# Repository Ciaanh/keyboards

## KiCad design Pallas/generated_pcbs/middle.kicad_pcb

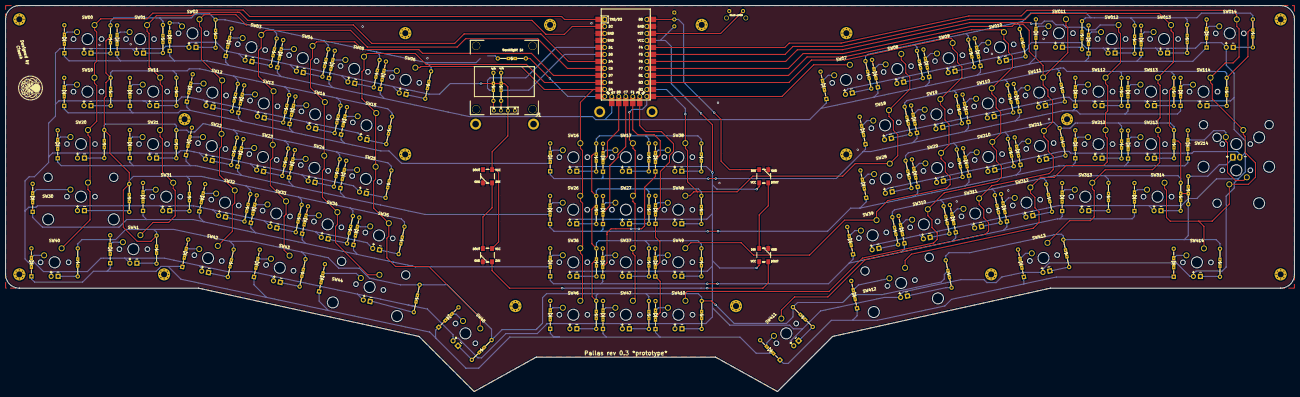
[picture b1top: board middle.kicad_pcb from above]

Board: 2 copper layers, 467.5 x 140.0 mm, 259 parts (1 on the bottom side), 182 nets.

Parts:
D00, D01, D02, D03, D04, D05, D06, D07, D08, D09, D010, D10, D11, D011, D12, D012, D13, D013, D14, D014, D15, D16, D17, D18, D19, D20, D21, D22, D23, D24, D25, D26, D27, D28, D29, D30, D31, D32, D33, D34, D35, D36, D37, D38, D39, D40, D41, D42, D43, D44, D45, D46, D47, D48, D49, D110, D111, D112, D113, D114, D210, D211, D212, D213, D214, D310, D311, D312, D313, D314, D410, D411, D412, D413, D414: Diode; Diode_SMD_THT
J1: OLED; OLED_128x64_I2C
J2: RGB_LED; conn_3pins
LogoBaseMiddleTop: LOGO; Ciaanh_signature
LogoMiddle2: LOGO; athena
MountBaseMiddleTop0, MountBaseMiddleTop2, MountBaseMiddleTop3, MountBaseMiddleTop4, MountBaseMiddleTop5, MountBaseMiddleTop6, MountBaseMiddleTop7, MountBaseMiddleTop8, MountBaseMiddleTop9, MountBaseMiddleTop10, MountBaseMiddleTop11, MountBaseMiddleTop12, MountBaseMiddleTop13, MountBaseMiddleTop14, MountBaseMiddleTop15, MountBaseMiddleTop15#2: MountingHole; MountingHole_2.2mm_M2_Pad_Via
MountForMiddle1: HOLE; MountingHole_2.4mm_M2_Pad
MountMiddle1, MountMiddle2, MountMiddle3: HOLE; MountingHole_2.4mm_M2_Pad
Q1: IRLML6344TRPbF; SOT23-3_HSOL_Back
R00, R01, R02, R03, R04, R05, R06, R07, R08, R09, R10, R010, R11, R011, R012, R12, R13, R013, R014, R14, R15, R16, R17, R18, R19, R20, R21, R22, R23, R24, R25, R26, R27, R28, R29, R30, R31, R32, R33, R34, R35, R36, R37, R38, R39, R40, R41, R42, R43, R44, R45, R46, R47, R48, R49, R110, R111, R112, R113, R114, R210, R211, R212, R213, R214, R310, R311, R312, R313, R314, R410, R411, R412, R413, R414: 470; Resistors_SMD_THT
R1, R2: 4.7k; Resistors_SMD_THT
R3: 1K; Resistors_SMD_THT
RGB1, RGB2, RGB3, RGB4: WS2812B; WS2812B_Front
RSW0: SW_RST
SW00, SW01, SW02, SW03, SW04, SW05, SW06, SW07, SW08, SW09, SW010, SW011, SW11, SW012, SW12, SW013, SW13, SW014, SW14, SW15, SW16, SW17, SW18, SW19, SW21, SW22, SW23, SW24, SW25, SW26, SW27, SW28, SW29, SW31, SW32, SW33, SW34, SW35, SW36, SW37, SW38, SW39, SW43, SW46, SW47, SW48, SW49, SW110, SW111, SW112, SW113, SW114, SW210, SW211, SW212, SW213, SW310, SW311, SW312, SW313, SW410: SW_PUSH; SW_Cherry_MX_1.00u_PCB
SW10: SW_PUSH; SW_Cherry_MX_1.50u_PCB
SW20, SW314: SW_PUSH; SW_Cherry_MX_1.75u_PCB
SW30: SW_PUSH; SW_Cherry_MX_2.25u_PCB
SW40, SW41, SW42, SW45, SW411, SW413, SW414: SW_PUSH; SW_Cherry_MX_1.25u_PCB
SW44: SW_PUSH; SW_Cherry_MX_2.00u_PCB
SW214: SW_PUSH; SW_Cherry_MX_2.25u_ISO_PCB
SW412: SW_PUSH; SW_Cherry_MX_2.75u_PCB
U1: Elite-C; Elite-C-castellated-29pin-holes

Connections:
Backlight: R3.2, U1.12
GND: J1.1, J2.1, Q1.2, RGB1.3, RGB2.3, RGB3.3, RGB4.3, RSW0.1, U1.3, U1.4, U1.23
LED: Q1.3, R00.1, R01.1, R02.1, R03.1, R04.1, R05.1, R06.1, R07.1, R08.1, R09.1, R10.1, R010.1, R11.1, R011.1, R012.1, R12.1, R13.1, R013.1, R014.1, R14.1, R15.1, R16.1, R17.1, R18.1, R19.1, R20.1, R21.1, R22.1, R23.1, R24.1, R25.1, R26.1, R27.1, R28.1, R29.1, R30.1, R31.1, R32.1, R33.1, R34.1, R35.1, R36.1, R37.1, R38.1, R39.1, R40.1, R41.1, R42.1, R43.1, R44.1, R45.1, R46.1, R47.1, R48.1, R49.1, R110.1, R111.1, R112.1, R113.1, R114.1, R210.1, R211.1, R212.1, R213.1, R214.1, R310.1, R311.1, R312.1, R313.1, R314.1, R410.1, R411.1, R412.1, R413.1, R414.1
unnamed: D00.2, SW00.2
unnamed: D01.2, SW01.2
unnamed: D02.2, SW02.2
unnamed: D03.2, SW03.2
unnamed: D04.2, SW04.2
unnamed: D05.2, SW05.2
unnamed: D06.2, SW06.2
unnamed: D07.2, SW07.2
unnamed: D08.2, SW08.2
unnamed: D09.2, SW09.2
unnamed: D010.2, SW010.2
unnamed: D10.2, SW10.2
unnamed: D011.2, SW011.2
unnamed: D11.2, SW11.2
unnamed: D012.2, SW012.2
unnamed: D12.2, SW12.2
unnamed: D013.2, SW013.2
unnamed: D13.2, SW13.2
unnamed: D014.2, SW014.2
unnamed: D14.2, SW14.2
unnamed: D15.2, SW15.2
unnamed: D16.2, SW16.2
unnamed: D17.2, SW17.2
unnamed: D18.2, SW18.2
unnamed: D19.2, SW19.2
unnamed: D20.2, SW20.2
unnamed: D21.2, SW21.2
unnamed: D22.2, SW22.2
unnamed: D23.2, SW23.2
unnamed: D24.2, SW24.2
unnamed: D25.2, SW25.2
unnamed: D26.2, SW26.2
unnamed: D27.2, SW27.2
unnamed: D28.2, SW28.2
unnamed: D29.2, SW29.2
unnamed: D30.2, SW30.2
unnamed: D31.2, SW31.2
unnamed: D32.2, SW32.2
unnamed: D33.2, SW33.2
unnamed: D34.2, SW34.2
unnamed: D35.2, SW35.2
unnamed: D36.2, SW36.2
unnamed: D37.2, SW37.2
unnamed: D38.2, SW38.2
unnamed: D39.2, SW39.2
unnamed: D40.2, SW40.2
unnamed: D41.2, SW41.2
unnamed: D42.2, SW42.2
unnamed: D43.2, SW43.2
unnamed: D44.2, SW44.2
unnamed: D45.2, SW45.2
unnamed: D46.2, SW46.2
unnamed: D47.2, SW47.2
unnamed: D48.2, SW48.2
unnamed: D49.2, SW49.2
unnamed: D110.2, SW110.2
unnamed: D111.2, SW111.2
unnamed: D112.2, SW112.2
unnamed: D113.2, SW113.2
unnamed: D114.2, SW114.2
unnamed: D210.2, SW210.2
unnamed: D211.2, SW211.2
unnamed: D212.2, SW212.2
unnamed: D213.2, SW213.2
unnamed: D214.2, SW214.2
unnamed: D310.2, SW310.2
unnamed: D311.2, SW311.2
unnamed: D312.2, SW312.2
unnamed: D313.2, SW313.2
unnamed: D314.2, SW314.2
unnamed: D410.2, SW410.2
unnamed: D411.2, SW411.2
unnamed: D412.2, SW412.2
unnamed: D413.2, SW413.2
unnamed: D414.2, SW414.2
unnamed: Q1.1, R3.1
unnamed: R00.2, SW00.4
unnamed: R01.2, SW01.4
unnamed: R02.2, SW02.4
unnamed: R03.2, SW03.4
unnamed: R04.2, SW04.4
unnamed: R05.2, SW05.4
unnamed: R06.2, SW06.4
unnamed: R07.2, SW07.4
unnamed: R08.2, SW08.4
unnamed: R09.2, SW09.4
unnamed: R010.2, SW010.4
unnamed: R10.2, SW10.4
unnamed: R011.2, SW011.4
unnamed: R11.2, SW11.4
unnamed: R012.2, SW012.4
unnamed: R12.2, SW12.4
unnamed: R013.2, SW013.4
unnamed: R13.2, SW13.4
unnamed: R014.2, SW014.4
unnamed: R14.2, SW14.4
unnamed: R15.2, SW15.4
unnamed: R16.2, SW16.4
unnamed: R17.2, SW17.4
unnamed: R18.2, SW18.4
unnamed: R19.2, SW19.4
unnamed: R20.2, SW20.4
unnamed: R21.2, SW21.4
unnamed: R22.2, SW22.4
unnamed: R23.2, SW23.4
unnamed: R24.2, SW24.4
unnamed: R25.2, SW25.4
unnamed: R26.2, SW26.4
unnamed: R27.2, SW27.4
unnamed: R28.2, SW28.4
unnamed: R29.2, SW29.4
unnamed: R30.2, SW30.4
unnamed: R31.2, SW31.4
unnamed: R32.2, SW32.4
unnamed: R33.2, SW33.4
unnamed: R34.2, SW34.4
unnamed: R35.2, SW35.4
unnamed: R36.2, SW36.4
unnamed: R37.2, SW37.4
unnamed: R38.2, SW38.4
unnamed: R39.2, SW39.4
unnamed: R40.2, SW40.4
unnamed: R41.2, SW41.4
unnamed: R42.2, SW42.4
unnamed: R43.2, SW43.4
unnamed: R44.2, SW44.4
unnamed: R45.2, SW45.4
unnamed: R46.2, SW46.4
unnamed: R47.2, SW47.4
unnamed: R48.2, SW48.4
unnamed: R49.2, SW49.4
unnamed: R110.2, SW110.4
unnamed: R111.2, SW111.4
unnamed: R112.2, SW112.4
unnamed: R113.2, SW113.4
unnamed: R114.2, SW114.4
unnamed: R210.2, SW210.4
unnamed: R211.2, SW211.4
unnamed: R212.2, SW212.4
unnamed: R213.2, SW213.4
unnamed: R214.2, SW214.4
unnamed: R310.2, SW310.4
unnamed: R311.2, SW311.4
unnamed: R312.2, SW312.4
unnamed: R313.2, SW313.4
unnamed: R314.2, SW314.4
unnamed: R410.2, SW410.4
unnamed: R411.2, SW411.4
unnamed: R412.2, SW412.4
unnamed: R413.2, SW413.4
unnamed: R414.2, SW414.4
unnamed: RGB1.2, RGB2.4
unnamed: RGB2.2, RGB3.4
unnamed: RGB3.2, RGB4.4
RESET: RSW0.2, U1.22
RGB: J2.2, RGB1.4, U1.24
SCL: J1.3, R2.2, U1.6
SDA: J1.4, R1.2, U1.5
VCC: J1.2, J2.3, R1.1, R2.1, RGB1.1, RGB2.1, RGB3.1, RGB4.1, SW00.3, SW01.3, SW02.3, SW03.3, SW04.3, SW05.3, SW06.3, SW07.3, SW08.3, SW09.3, SW010.3, SW10.3, SW011.3, SW11.3, SW012.3, SW12.3, SW013.3, SW13.3, SW014.3, SW14.3, SW15.3, SW16.3, SW17.3, SW18.3, SW19.3, SW20.3, SW21.3, SW22.3, SW23.3, SW24.3, SW25.3, SW26.3, SW27.3, SW28.3, SW29.3, SW30.3, SW31.3, SW32.3, SW33.3, SW34.3, SW35.3, SW36.3, SW37.3, SW38.3, SW39.3, SW40.3, SW41.3, SW42.3, SW43.3, SW44.3, SW45.3, SW46.3, SW47.3, SW48.3, SW49.3, SW110.3, SW111.3, SW112.3, SW113.3, SW114.3, SW210.3, SW211.3, SW212.3, SW213.3, SW214.3, SW310.3, SW311.3, SW312.3, SW313.3, SW314.3, SW410.3, SW411.3, SW412.3, SW413.3, SW414.3, U1.21
col0: SW00.1, SW10.1, SW20.1, SW30.1, SW40.1, U1.1
col1: SW01.1, SW11.1, SW21.1, SW31.1, SW41.1, U1.2
col2: SW02.1, SW12.1, SW22.1, SW32.1, SW42.1, U1.7
col3: SW03.1, SW13.1, SW23.1, SW33.1, SW43.1, U1.8
col4: SW04.1, SW14.1, SW24.1, SW34.1, SW44.1, U1.9
col5: SW05.1, SW15.1, SW25.1, SW35.1, SW45.1, U1.10
col6: SW06.1, SW16.1, SW26.1, SW36.1, SW46.1, U1.11
col7: SW07.1, SW17.1, SW27.1, SW37.1, SW47.1, U1.13
col8: SW08.1, SW18.1, SW28.1, SW38.1, SW48.1, U1.14
col9: SW09.1, SW19.1, SW29.1, SW39.1, SW49.1, U1.15
col10: SW010.1, SW110.1, SW210.1, SW310.1, SW410.1, U1.16
col11: SW011.1, SW111.1, SW211.1, SW311.1, SW411.1, U1.17
col12: SW012.1, SW112.1, SW212.1, SW312.1, SW412.1, U1.18
col13: SW013.1, SW113.1, SW213.1, SW313.1, SW413.1, U1.19
col14: SW014.1, SW114.1, SW214.1, SW314.1, SW414.1, U1.20
row0: D00.1, D01.1, D02.1, D03.1, D04.1, D05.1, D06.1, D07.1, D08.1, D09.1, D010.1, D011.1, D012.1, D013.1, D014.1, U1.25
row1: D10.1, D11.1, D12.1, D13.1, D14.1, D15.1, D16.1, D17.1, D18.1, D19.1, D110.1, D111.1, D112.1, D113.1, D114.1, U1.26
row2: D20.1, D21.1, D22.1, D23.1, D24.1, D25.1, D26.1, D27.1, D28.1, D29.1, D210.1, D211.1, D212.1, D213.1, D214.1, U1.27
row3: D30.1, D31.1, D32.1, D33.1, D34.1, D35.1, D36.1, D37.1, D38.1, D39.1, D310.1, D311.1, D312.1, D313.1, D314.1, U1.28
row4: D40.1, D41.1, D42.1, D43.1, D44.1, D45.1, D46.1, D47.1, D48.1, D49.1, D410.1, D411.1, D412.1, D413.1, D414.1, U1.29
